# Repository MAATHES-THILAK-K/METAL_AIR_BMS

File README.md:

# 🔋 Metal-Air Single Cell Battery Management System 

---

## 📖 Overview

The **Metal-Air Single Cell Battery Management System (BMS)** is a custom embedded system designed to safely monitor and protect a single-cell Metal-Air battery. The project is built around the **STM32G0B1CBT6** microcontroller and provides real-time monitoring of battery voltage, current, temperature, and hydrogen gas concentration while implementing multiple protection mechanisms to ensure reliable battery operation.

The repository contains the complete embedded firmware, hardware design files, Python monitoring application, and supporting documentation required to reproduce the project.

---

## ✨ Key Features

* STM32G0B1CBT6 Microcontroller
* INA226 High-Precision Current & Bus Voltage Monitoring
* NTC Thermistor-Based Temperature Measurement
* Hydrogen Gas Sensor Monitoring
* Real-Time Fault Detection
* Over-Current Protection (OCP)
* Under-Voltage Protection (UVP)
* Over-Temperature Protection (OTP)
* UART Communication
* Python-Based Monitoring & Data Logging
* Audible Fault Indication (Buzzer)
* MOSFET-Based Load Disconnect

---

## 🏗️ System Architecture

```text
                  +----------------------------+
                  |    Metal-Air Battery       |
                  +-------------+--------------+
                                |
                 +--------------v--------------+
                 |       STM32G0B1CBT6         |
                 +--------------+--------------+
                                |
     +------------+-------------+------------+--------------+
     |            |                          |              |
     |            |                          |              |
+----v----+ +-----v-----+            +-------v------+ +-----v------+
| INA226  | | NTC Sensor|            | H₂ Sensor    | | UART Debug |
| Current | |Temperature|            | Monitoring   | | / Logging  |
+---------+ +-----------+            +--------------+ +------------+
       |                                           |
       +----------------------+--------------------+
                              |
                      +-------v--------+
                      | Protection     |
                      | Decision Logic |
                      +-------+--------+
                              |
                   +----------v-----------+
                   | MOSFET Load Control  |
                   +----------------------+
```

---

## 🔧 Hardware

### Microcontroller

* STM32G0B1CBT6

### Sensors

* INA226 Current & Bus Voltage Sensor
* NTC Thermistor
* Hydrogen Gas Sensor

### Output Devices

* Protection MOSFET
* Buzzer

### Communication

* UART Serial Interface

---

## 💻 Firmware

The embedded firmware continuously performs the following tasks:

* Battery Voltage Measurement
* Current Measurement
* Temperature Monitoring
* Hydrogen Gas Detection
* Fault Monitoring
* Protection Decision Making
* MOSFET Control
* UART Data Transmission for Monitoring

---

## 📂 Project Structure

```text
Metal-Air-Single-Cell-BMS/
│
├── Firmware/
│   └── Metal_Air_BMS.ino
│
├── Python/
│   └── BMS_Monitor.py
│
├── Hardware/
│   ├── Schematic.pdf
│   ├── PCB.pdf
│   ├── PCB_Render.png
│   ├── PCB_Top.png
│   ├── PCB_Bottom.png
│   ├── Gerber.zip
│   ├── BOM.xlsx
│   └── Pick_and_Place.csv
│
├── Images/
│   ├── PCB_Render.png
│   ├── Completed_PCB.jpg
│   ├── Wiring_Diagram.png
│   └── Block_Diagram.png
│
├── README.md
├── requirements.txt
└── .gitignore
```

---

## 🚀 Getting Started

### Hardware

1. Assemble the PCB.
2. Connect the Metal-Air battery.
3. Connect the sensors.
4. Verify all wiring before powering the system.

### Firmware

Compile the firmware using the **Arduino IDE** with the **STM32 Arduino Core** installed.

Upload the firmware using:

* ST-Link
* UART Bootloader

---

## 🎯 Applications

* Metal-Air Battery Research
* Battery Safety Systems
* Embedded Systems Development
* Laboratory Testing
* Battery Performance Evaluation
* Educational and Research Projects

---

## 👨‍💻 Author

**MAATHES THILAK K**

Electronics and Communication Engineering

Anna University, MIT Campus, Chennai

---
⭐ If you found this project useful, consider giving it a **Star**!

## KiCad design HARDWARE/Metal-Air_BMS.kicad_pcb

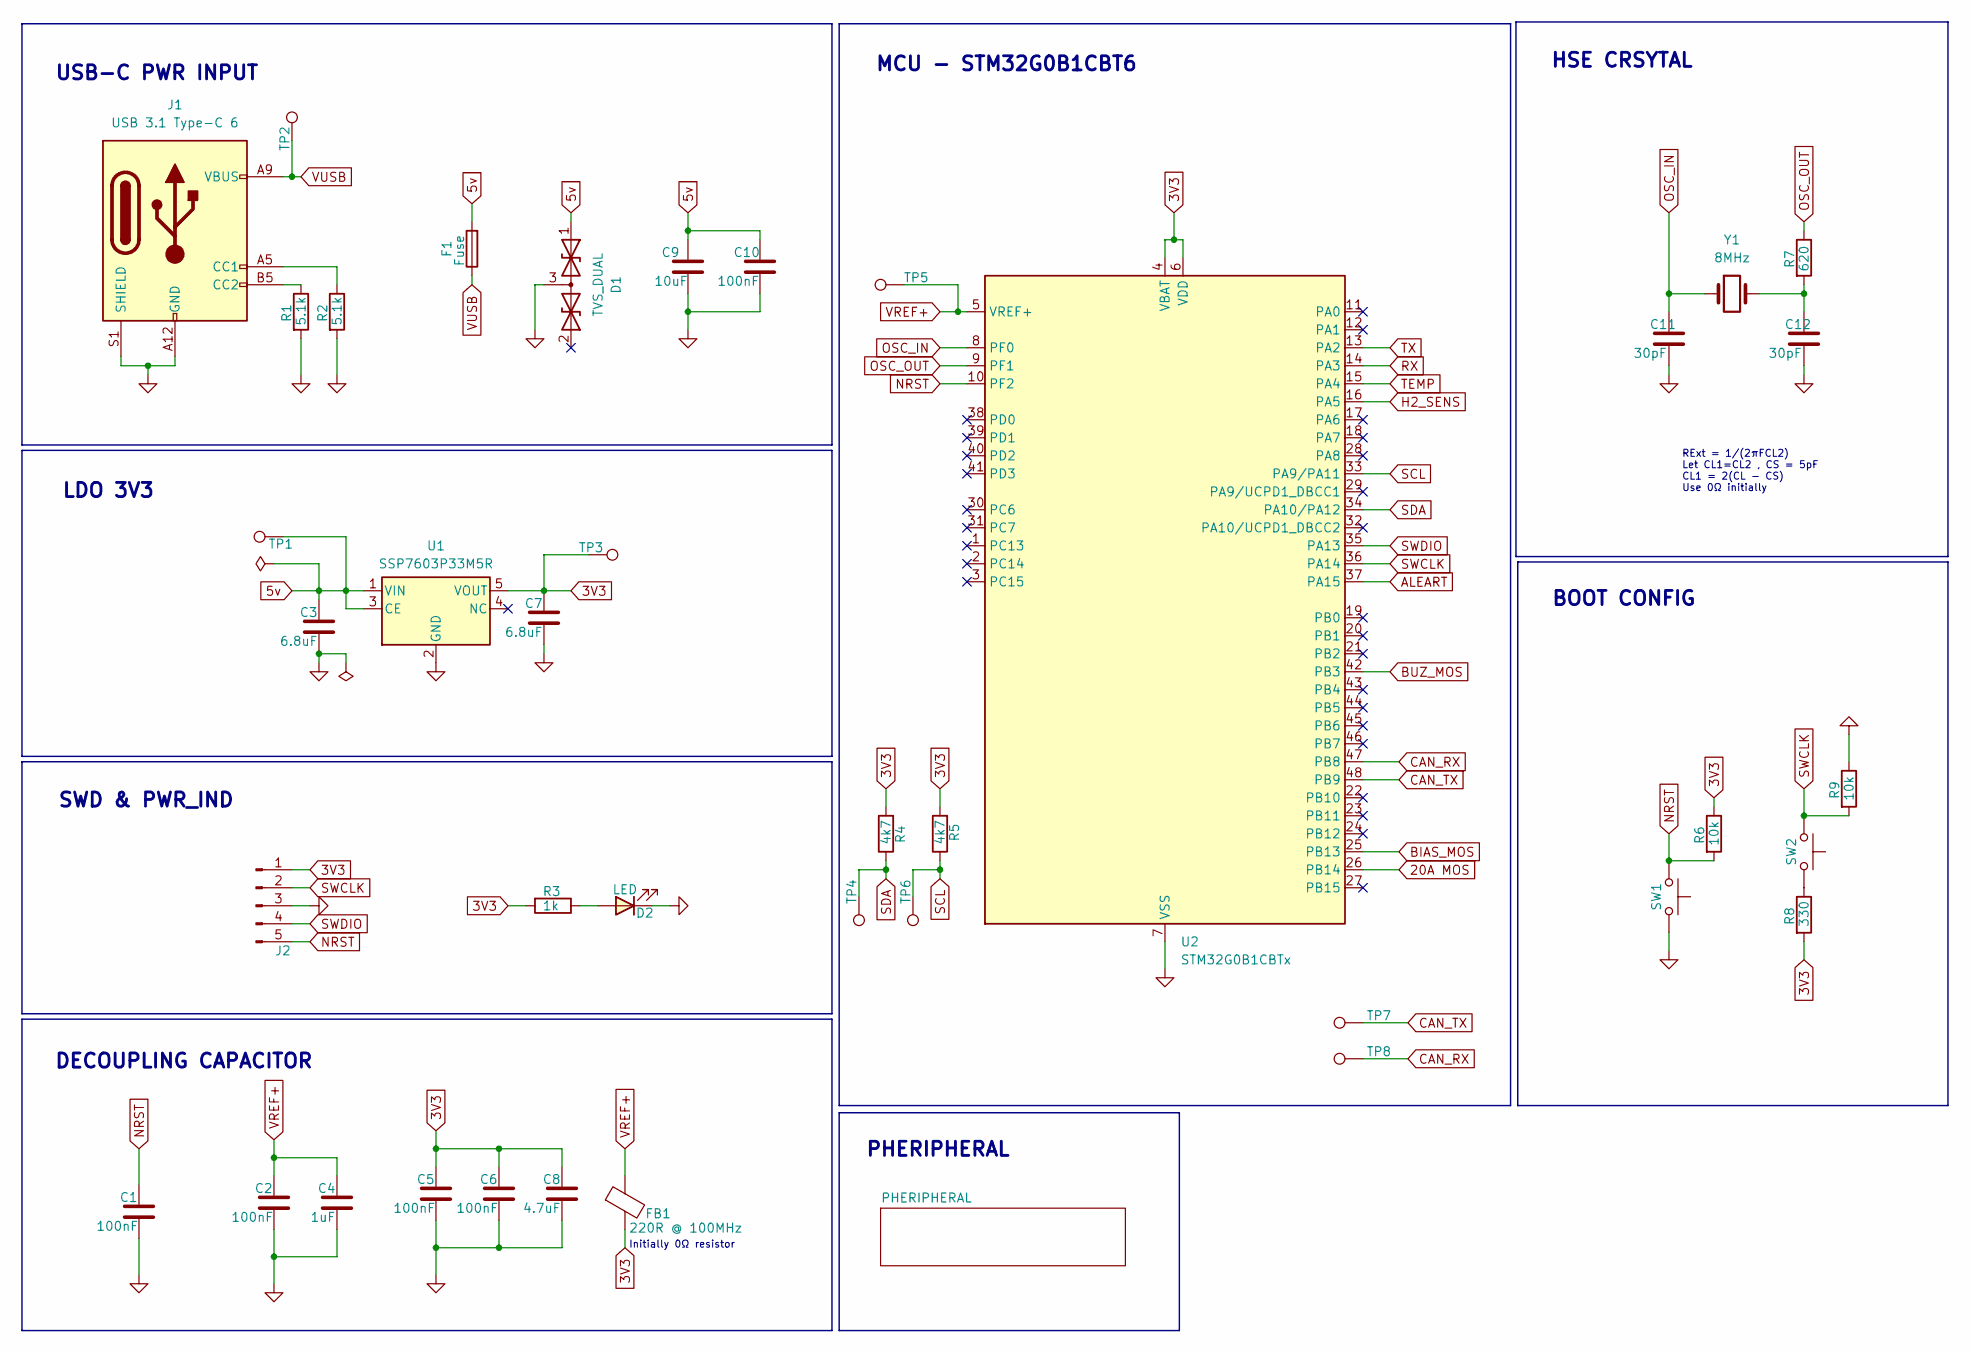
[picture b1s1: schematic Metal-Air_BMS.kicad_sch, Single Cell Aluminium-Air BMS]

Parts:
C1, C2, C5, C6: 100nF; C_0603_1608Metric
C3, C7: 6.8uF; C_1812_4532Metric_Pad1.57x3.40mm_HandSolder
C4: 1uF; C_0603_1608Metric
C8: 4.7uF; C_0603_1608Metric
C9: 10uF; C_0805_2012Metric_Pad1.18x1.45mm_HandSolder
C10: 100nF; C_0805_2012Metric_Pad1.18x1.45mm_HandSolder
C11, C12: 30pF; C_0805_2012Metric
D1: TVS_DUAL; SOT-23
D2: LED; LED_0805_2012Metric_Pad1.15x1.40mm_HandSolder
F1: Fuse; Fuse_0805_2012Metric_Pad1.15x1.40mm_HandSolder
FB1: 220R @ 100MHz; L_0603_1608Metric
J1: USB 3.1 Type-C 6; USB_C_Receptacle_HRO_TYPE-C-31-M-17
J2: 01x05; JST_GENERIC_5-PIN
R1, R2: 5.1k; R_0805_2012Metric_Pad1.20x1.40mm_HandSolder
R3: 1k; R_0805_2012Metric_Pad1.20x1.40mm_HandSolder
R4, R5: 4k7; R_0603_1608Metric
R6, R9: 10k; R_0805_2012Metric
R7: 620; R_0603_1608Metric
R8: 330; R_0805_2012Metric_Pad1.20x1.40mm_HandSolder
SW1, SW2: PUSH; SW_Tactile_SPST_NO_Straight_CK_PTS636Sx25SMTRLFS
TP1: 5V; TestPoint_Pad_D1.5mm
TP2: Vbus; TestPoint_Pad_D1.5mm
TP3: 3V3; TestPoint_Pad_D1.5mm
TP4: SDA; TestPoint_Pad_D1.5mm
TP5: Vref; TestPoint_Pad_D1.5mm
TP6: SCL; TestPoint_Pad_D1.5mm
TP7: TX; TestPoint_Pad_D1.5mm
TP8: RX; TestPoint_Pad_D1.5mm
U1: SSP7603P33M5R; SOT-23-5
U2: STM32G0B1CBTx; LQFP-48_7x7mm_P0.5mm
Y1: 8MHz; Crystal_SMD_5032-2Pin_5.0x3.2mm

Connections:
3V3: C5.1, C6.1, C7.1, C8.1, FB1.2, J2.1, R3.2, R4.2, R5.2, R6.1, R8.2, TP3.1, U1.5 (VOUT), U2.4 (VBAT), U2.6 (VDD); also elsewhere on the board
5v: C3.1, C9.1, C10.1, D1.1 (A1), F1.2, TP1.1, U1.1 (VIN), U1.3 (CE); also elsewhere on the board
20A MOS: U2.26 (PB14); also elsewhere on the board
ALEART: U2.37 (PA15); also elsewhere on the board
BIAS_MOS: U2.25 (PB13); also elsewhere on the board
BUZ_MOS: U2.42 (PB3); also elsewhere on the board
CAN_RX: TP8.1, U2.47 (PB8); also elsewhere on the board
CAN_TX: TP7.1, U2.48 (PB9); also elsewhere on the board
GND: C1.2, C2.2, C3.2, C4.2, C5.2, C6.2, C7.2, C8.2, C9.2, C10.2, C11.2, C12.2, D1.3 (common), D2.1 (K), J1.A12 (GND), J1.B12 (GND), J1.S1 (SHIELD), J2.3, R1.2, R2.2, R9.1, SW1.2, U1.2 (GND), U2.7 (VSS); also elsewhere on the board
H2_SENS: U2.16 (PA5); also elsewhere on the board
NRST: C1.1, J2.5, R6.2, SW1.1, U2.10 (PF2)
unnamed: C12.1, R7.2, Y1.2
unnamed: D2.2 (A), R3.1
unnamed: J1.A5 (CC1), R2.1
unnamed: J1.B5 (CC2), R1.1
unnamed: R8.1, SW2.2
OSC_IN: C11.1, U2.8 (PF0), Y1.1
OSC_OUT: R7.1, U2.9 (PF1)
RX: U2.14 (PA3); also elsewhere on the board
SCL: R5.1, TP6.1, U2.33 (PA9/PA11); also elsewhere on the board
SDA: R4.1, TP4.1, U2.34 (PA10/PA12); also elsewhere on the board
SWCLK: J2.2, R9.2, SW2.1, U2.36 (PA14)
SWDIO: J2.4, U2.35 (PA13)
TEMP: U2.15 (PA4); also elsewhere on the board
TX: U2.13 (PA2); also elsewhere on the board
VREF+: C2.1, C4.1, FB1.1, TP5.1, U2.5 (VREF+)
VUSB: F1.1, J1.A9 (VBUS), J1.B9 (VBUS), TP2.1

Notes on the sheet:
LDO 3V3
DECOUPLING CAPACITOR
RExt = 1/(2πFCL2) Let CL1=CL2 , CS = 5pF CL1 = 2(CL - CS) Use 0Ω initially
MCU - STM32G0B1CBT6
Initially 0Ω resistor
USB-C PWR INPUT
SWD & PWR_IND
HSE CRSYTAL
PHERIPHERAL
BOOT CONFIG

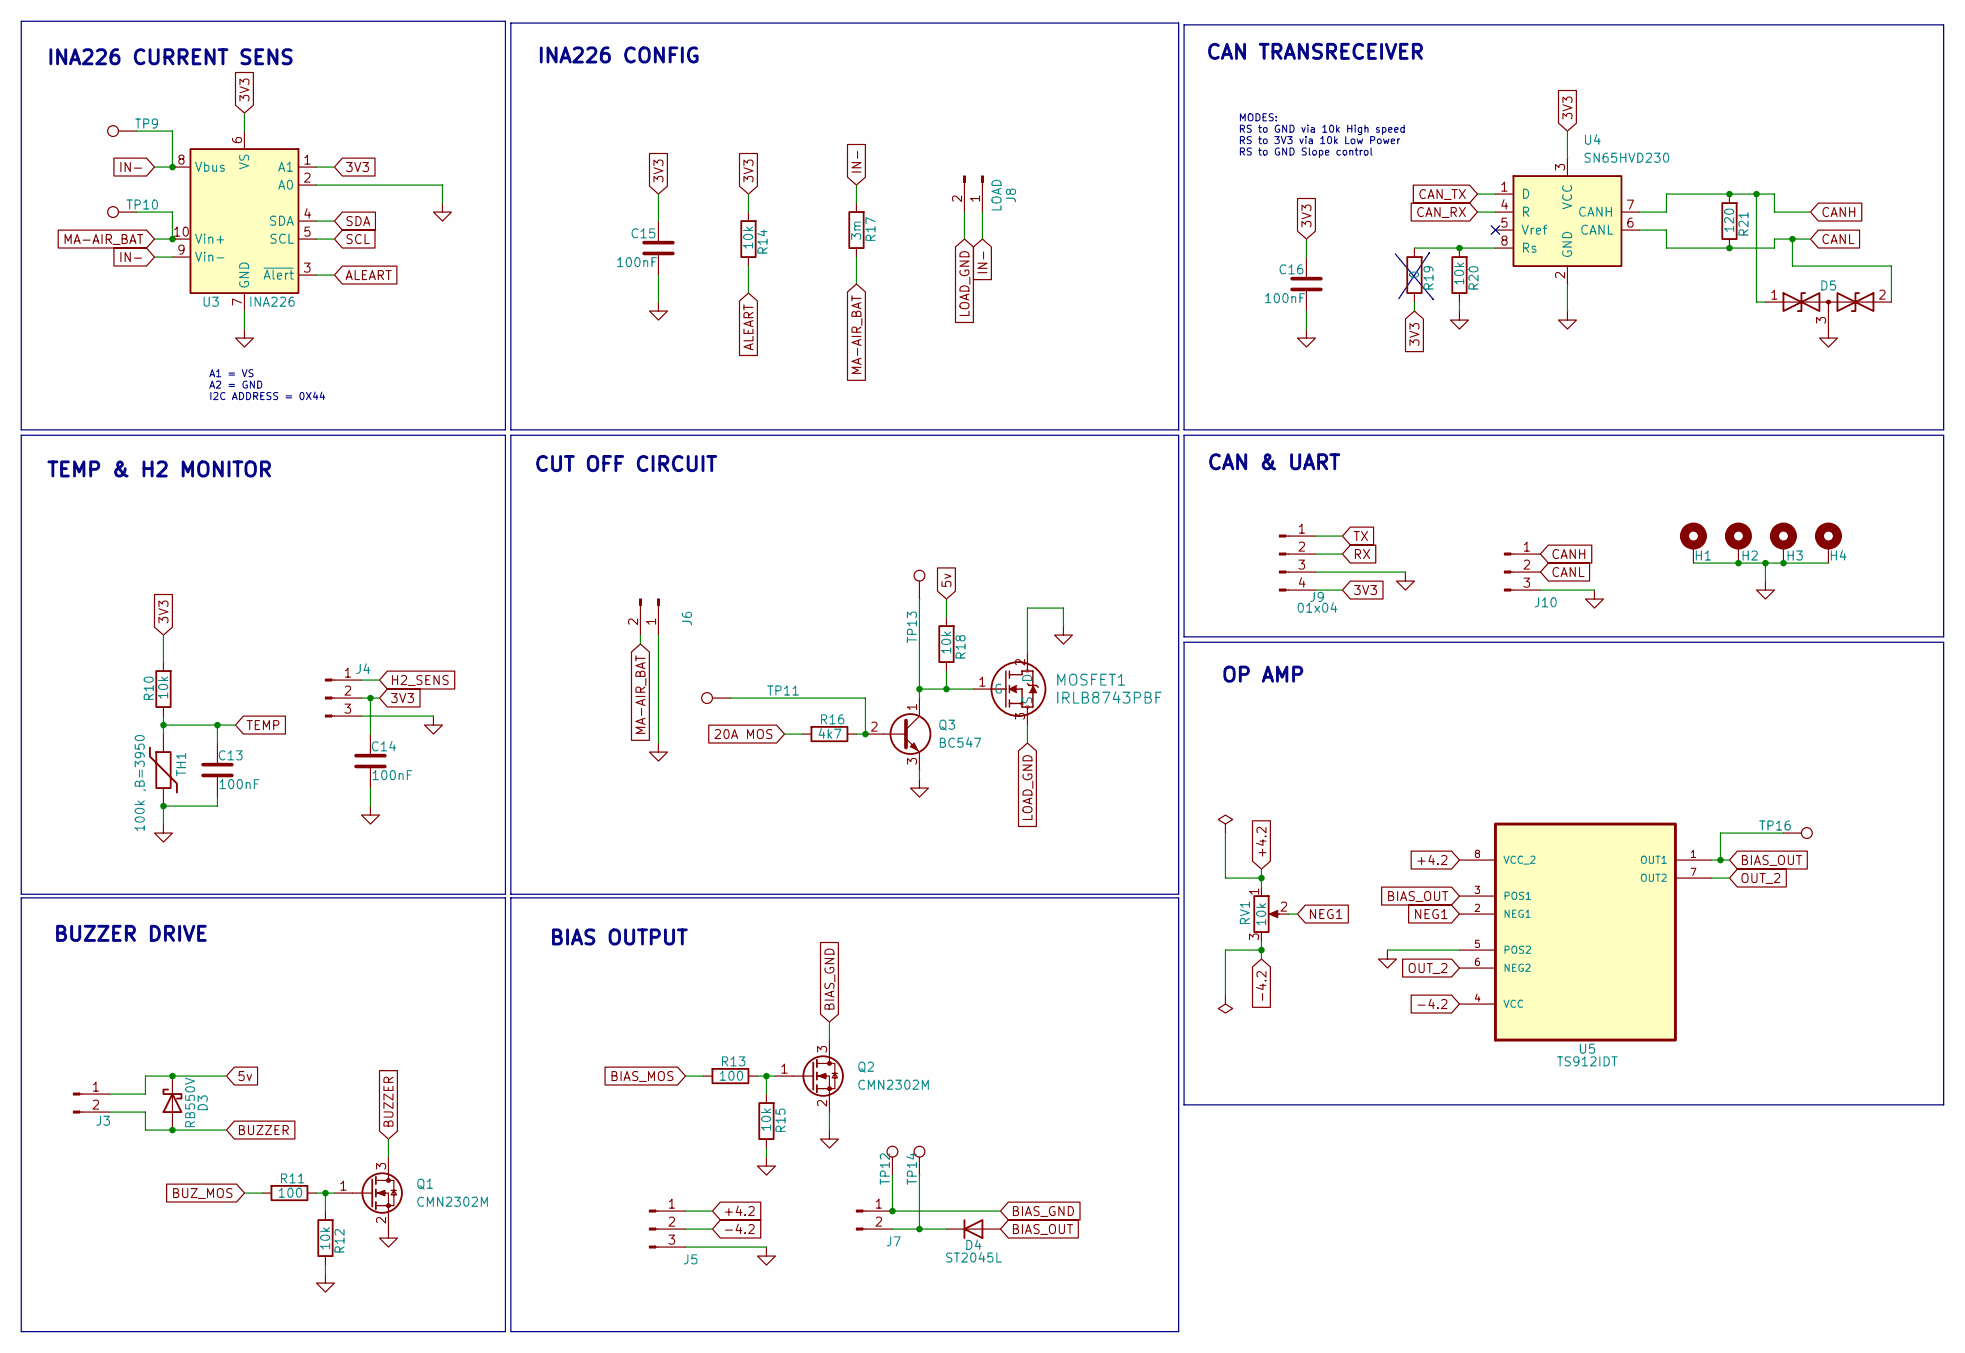
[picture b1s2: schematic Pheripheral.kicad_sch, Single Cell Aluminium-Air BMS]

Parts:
C13, C14, C15, C16: 100nF; C_0805_2012Metric_Pad1.18x1.45mm_HandSolder
D3: RB550V; D_SOD-323_HandSoldering
D4: ST2045L; TO-277A
D5: TVS_DUAL; SOT-23
H1, H2, H3, H4: MountingHole_Pad; MountingHole_2.2mm_M2_Pad_Via
J3: 01x02; Buzzer_12x9.5RM6.0
J4: 01x03; JST_XH_S3B-XH-A_1x03_P2.50mm_Horizontal
J5, J10: 01x03; TerminalBlock_Xinya_XY308-2.54-3P_1x03_P2.54mm_Horizontal
J6: 01x02; TerminalBlock_Xinya_XY845A-9.50-2P_1x02_P9.50mm
J7: 01x02; TerminalBlock_Xinya_XY308-2.54-2P_1x02_P2.54mm_Horizontal
J8: LOAD; TerminalBlock_Xinya_XY845A-9.50-2P_1x02_P9.50mm
J9: 01x04; CONN-TH_4P-P2.50_WAFER-XH254WZ-4A
MOSFET1: IRLB8743PBF; TO-220-3_Vertical
Q1, Q2: CMN2302M; SOT-23
Q3: BC547; SOT-23
R10, R12, R14, R15, R18, R20: 10k; R_0805_2012Metric_Pad1.20x1.40mm_HandSolder
R11, R13: 100; R_0805_2012Metric_Pad1.20x1.40mm_HandSolder
R16: 4k7; R_0805_2012Metric_Pad1.20x1.40mm_HandSolder
R17: 3m; R_2816_7142Metric_Pad3.20x4.45mm_HandSolder
R19: 0; R_0805_2012Metric_Pad1.20x1.40mm_HandSolder
R21: 120; R_0805_2012Metric_Pad1.20x1.40mm_HandSolder
RV1: 10k; Potentiometer_Bourns_3296X_Horizontal
TH1: 100k ,B=3950; TerminalBlock_Xinya_XY308-2.54-2P_1x02_P2.54mm_Horizontal
TP9: IN-; TestPoint_Pad_D1.5mm
TP10: VBUS; TestPoint_Pad_D1.5mm
TP11: NPN-B; TestPoint_Pad_D1.5mm
TP12: BIAS-G; TestPoint_Pad_D1.5mm
TP13: NPN-C; TestPoint_Pad_D1.5mm
TP14: BIAS-D; TestPoint_Pad_D1.5mm
TP16: BIAS-OUT; TestPoint_Pad_D1.5mm
U3: INA226
U4: SN65HVD230; SOIC-8_3.9x4.9mm_P1.27mm
U5: TS912IDT; TS9121IDT; MPN TS912ID

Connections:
3V3: C14.1, C15.1, C16.1, J4.2, J9.4, R10.2, R14.2, R19.1, U3.1 (A1), U3.6 (VS), U4.3 (VCC); also elsewhere on the board
5v: D3.1 (K), J3.1, R18.2; also elsewhere on the board
20A MOS: R16.2; also elsewhere on the board
+4.2: J5.1, RV1.1, U5.8 (VCC_2)
-4.2: J5.2, RV1.3, U5.4 (VCC)
ALEART: R14.1, U3.3 (~Alert); also elsewhere on the board
BIAS_GND: J7.1, Q2.3 (D), TP12.1
BIAS_MOS: R13.2; also elsewhere on the board
BIAS_OUT: D4.1 (A), D4.2 (A), TP16.1, U5.1 (OUT1), U5.3 (POS1)
BUZZER: D3.2 (A), J3.2, Q1.3 (D)
BUZ_MOS: R11.2; also elsewhere on the board
CANH: D5.1 (A1), J10.1, R21.2, U4.7 (CANH)
CANL: D5.2 (A2), J10.2, R21.1, U4.6 (CANL)
CAN_RX: U4.4 (R); also elsewhere on the board
CAN_TX: U4.1 (D); also elsewhere on the board
GND: C13.2, C14.2, C15.2, C16.2, D5.3 (common), H1.1, H2.1, H3.1, H4.1, J4.3, J5.3, J6.1, J9.3, J10.3, MOSFET1.2 (D), Q1.2 (S), Q2.2 (S), Q3.3 (E), R12.1, R15.1, R20.1, TH1.2, U3.2 (A0), U3.7 (GND), U4.2 (GND), U5.5 (POS2); also elsewhere on the board
H2_SENS: J4.1; also elsewhere on the board
IN-: J8.1, R17.2, TP9.1, U3.8 (Vbus), U3.9 (Vin-)
LOAD_GND: J8.2, MOSFET1.3 (S)
MA-AIR_BAT: J6.2, R17.1, TP10.1, U3.10 (Vin+)
NEG1: RV1.2, U5.2 (NEG1)
unnamed: D4.3 (K), J7.2, TP14.1
unnamed: MOSFET1.1 (G), Q3.1 (C), R18.1, TP13.1
unnamed: Q1.1 (G), R11.1, R12.2
unnamed: Q2.1 (G), R13.1, R15.2
unnamed: Q3.2 (B), R16.1, TP11.1
unnamed: R19.2, R20.2, U4.8 (Rs)
OUT_2: U5.6 (NEG2), U5.7 (OUT2)
RX: J9.2; also elsewhere on the board
SCL: U3.5 (SCL); also elsewhere on the board
SDA: U3.4 (SDA); also elsewhere on the board
TEMP: C13.1, R10.1, TH1.1; also elsewhere on the board
TX: J9.1; also elsewhere on the board

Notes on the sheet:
BIAS OUTPUT
BUZZER DRIVE
OP AMP
CAN & UART
CAN TRANSRECEIVER
TEMP & H2 MONITOR
INA226 CURRENT SENS
CUT OFF CIRCUIT
INA226 CONFIG
A1 = VS A2 = GND I2C ADDRESS = 0X44
MODES: RS to GND via 10k High speed RS to 3V3 via 10k Low Power RS to GND Slope control

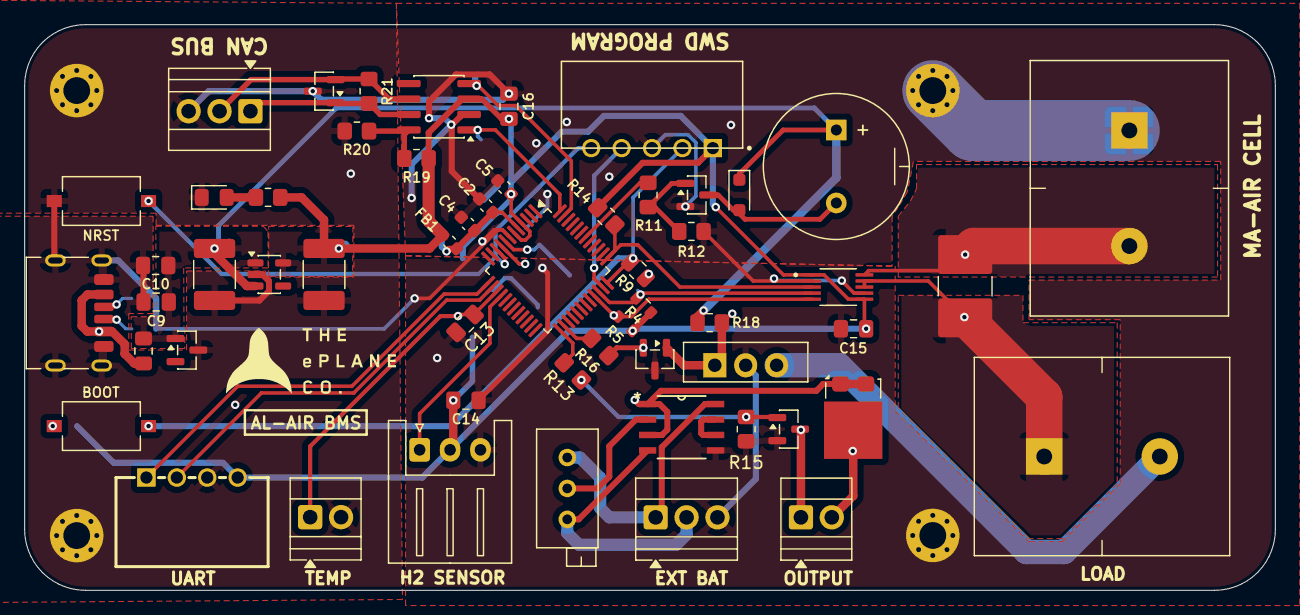
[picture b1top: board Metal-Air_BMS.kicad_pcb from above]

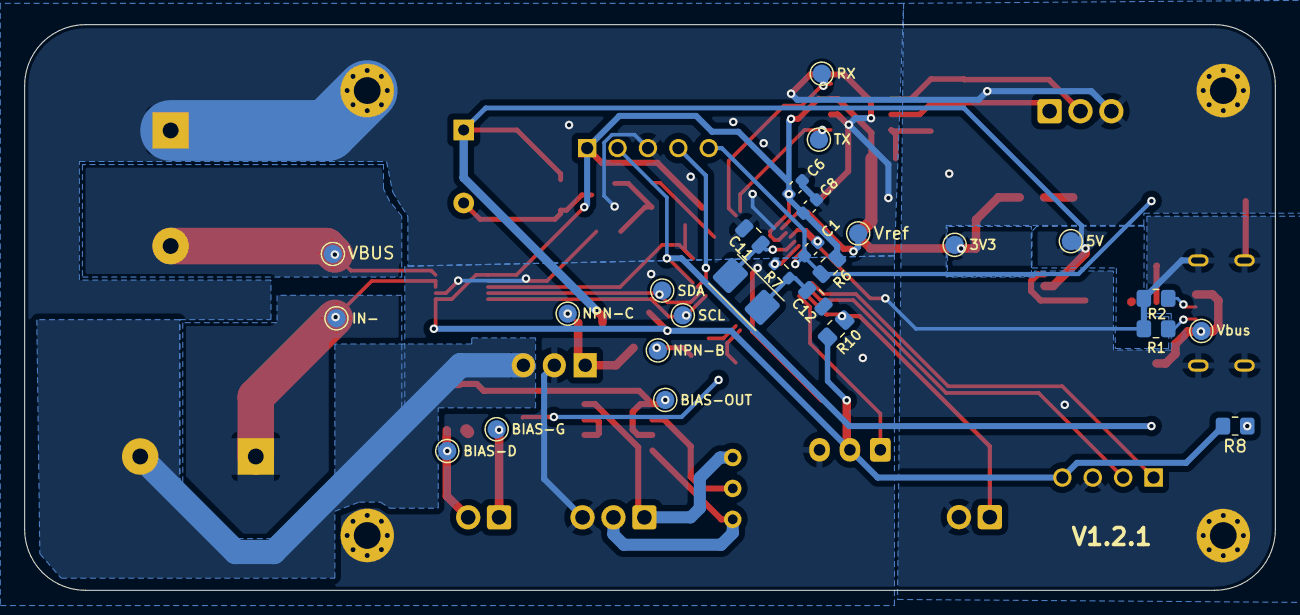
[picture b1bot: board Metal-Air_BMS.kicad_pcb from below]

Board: 2 copper layers, 102.8 x 46.5 mm, 87 parts (27 on the bottom side), 45 nets.

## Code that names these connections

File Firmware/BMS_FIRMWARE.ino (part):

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#include <math.h>

// ---- pins ----
#define SDA_PIN PA12
#define SCL_PIN PA11
#define ALERT_PIN PA15
#define BUZZER_PIN PB3
#define MOSFET_PIN PB14
#define TEMP_PIN PA4
#define H2_PIN PA5

HardwareSerial Serial1(PA3, PA2);

// ---- INA226 registers ----
#define INA226_ADDR 0x44
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    if (millis() - lastBuzz >= BUZZ_PERIOD_MS) {
      lastBuzz = millis();
      buzzState = !buzzState;
      digitalWrite(BUZZER_PIN, buzzState ? HIGH : LOW);
    }
  } else {
    digitalWrite(BUZZER_PIN, LOW);
  }
}

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
void setup() {
  pinMode(ALERT_PIN, INPUT_PULLUP);
  pinMode(BUZZER_PIN, OUTPUT);
  pinMode(MOSFET_PIN, OUTPUT);
  digitalWrite(BUZZER_PIN, LOW);
  digitalWrite(MOSFET_PIN, LOW);

  analogReadResolution(12);
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

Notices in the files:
README.md:
License: PolyForm Noncommercial 1.0.0
